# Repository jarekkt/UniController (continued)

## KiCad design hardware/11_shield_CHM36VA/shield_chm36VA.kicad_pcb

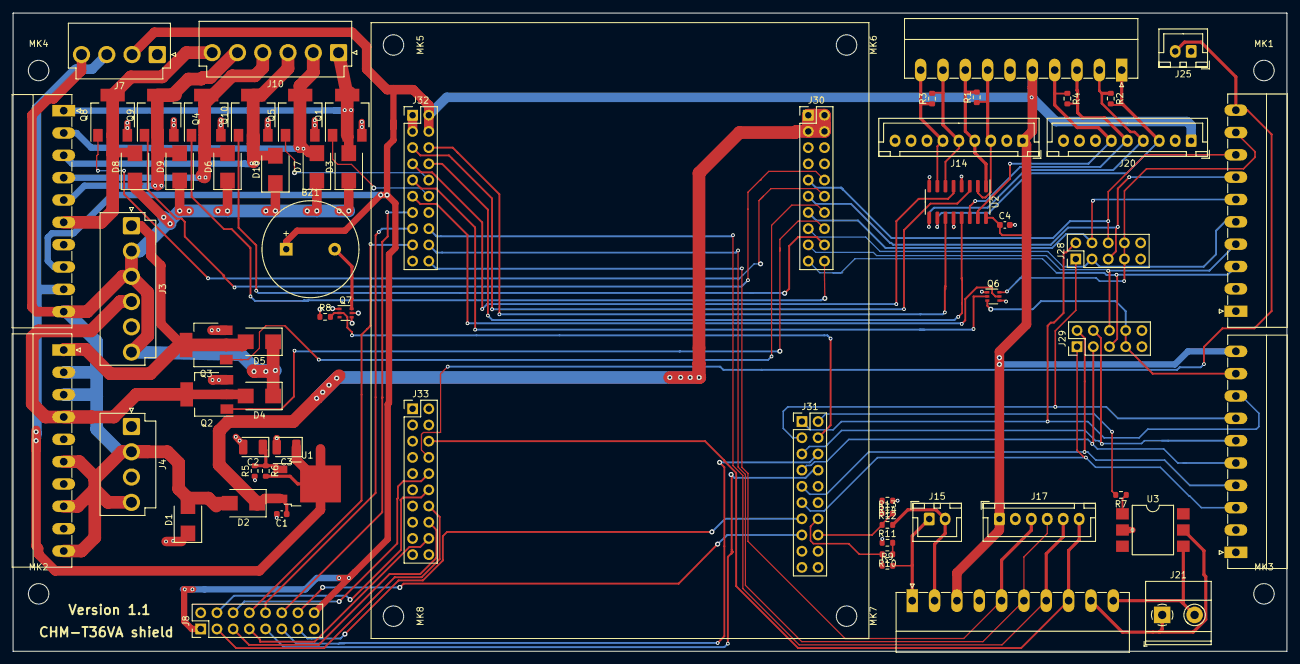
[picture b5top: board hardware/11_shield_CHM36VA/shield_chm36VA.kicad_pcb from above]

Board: 2 copper layers, 199.6 x 100.0 mm, 73 parts (0 on the bottom side), 80 nets.

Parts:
BZ1: Buzzer; Buzzer_15x7.5RM7.6
C1, C4: 100n; C_0603_1608Metric
C2: 10uf; CP_EIA-3528-21_Kemet-B
C3: 1uf; CP_EIA-3528-21_Kemet-B
D1: SMCJ24CA; D_SMB
D2, D3, D4, D5, D6, D7, D8, D9, D10: SK56; D_SMB
J3, J10: Conn_01x06_Male; JST_VH_B6P-VH-B_1x06_P3.96mm_Vertical
J4, J7: Conn_01x04_Male; JST_VH_B4P-VH_1x04_P3.96mm_Vertical
J5, J11, J12, J23, J26, J27: Conn_01x10_Male; PhoenixContact_MC-G_10x3.50mm_Angled
J8: Conn_02x05_Odd_Even; PinHeader_2x08_P2.54mm_Vertical
J14, J20: Conn_01x09_Male; JST_XH_B9B-XH-A_1x09_P2.50mm_Vertical
J15, J25: Conn_01x02_Male; JST_XH_B2B-XH-A_1x02_P2.50mm_Vertical
J17: Conn_01x06_Male; JST_XH_B6B-XH-A_1x06_P2.50mm_Vertical
J21: Conn_01x02_Male; TerminalBlock_Phoenix_MKDS-1,5-2-5.08_1x02_P5.08mm_Horizont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
J28, J29: Conn_02x05_Odd_Even; PinHeader_2x05_P2.54mm_Vertical
J30, J31, J33: Conn_02x20_Odd_Even; PinHeader_2x10_P2.54mm_Vertical
J32: Conn_02x10_Odd_Even; PinHeader_2x10_P2.54mm_Vertical
MK1, MK1#2, MK2, MK2#2, MK3, MK3#2, MK6, MK6#2: Mounting_Hole; MountingHole_3.2mm_M3
Q1, Q2, Q3, Q4, Q5, Q8, Q9, Q10: IRLL2705PBF; SOT-223
Q6, Q7: BSS138BKS; SOT-363_SC-70-6
R1, R2, R3, R4: 120R; R_0603_1608Metric
R5, R8: 4k6; R_0603_1608Metric
R6: 1k; R_0603_1608Metric
R7: 220R; R_0603_1608Metric
R9, R10, R11, R12, R13, R14: 2k2; R_0603_1608Metric
U1: LM217_TO-252; TO-252-2
U2: AM26LS32ACD; SOIC-16_3.9x9.9mm_P1.27mm
U3: CNY17-1; SMDIP-6_W9.53mm

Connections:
+3V3: J32.1, J32.3
+5V: BZ1.1 (-), C4.1, J7.2, J8.1, J8.16, J11.8, J12.3, J14.1, J17.1, J20.1, J23.5, J27.10, J32.2, J32.4, U2.16 (VDD)
+7V: C3.1, J7.3, J11.9, R6.2, U1.2 (VO)
+24V: D1.2, D2.2 (A), D3.1 (K), D4.1 (K), D5.1 (K), D6.1 (K), D7.1 (K), D8.1 (K), D9.1 (K), D10.1 (K), J3.2, J3.3, J3.6, J4.2, J4.4, J5.2, J5.3, J5.6, J5.8, J5.10, J7.4, J11.10
/controller/CAM+: J12.9, J21.1, U3.5
/controller/CAM-: J12.10, J21.2, U3.4
/controller/DIR_A: J27.7, J28.1, J31.3
/controller/DIR_B: J27.5, J29.3, J31.7
/controller/DIR_C: J27.3, J29.1, J31.11
/controller/DIR_X: J26.7, J28.5, J30.11
/controller/DIR_Y: J26.5, J28.3, J30.15
/controller/DIR_Z: J26.3, J29.5, J30.19
/controller/ENA_ABC: J27.9, J29.7, J29.8, Q6.3 (D)
/controller/ENA_XYZ: J26.9, J28.7, J28.8, Q6.6 (D)
/controller/ENC_X_A+: J20.3, J23.1, R2.2, U2.10 (3A)
/controller/ENC_X_A-: J20.4, J23.2, R2.1, U2.9 (3B)
/controller/ENC_X_B+: J20.5, J23.3, R4.2, U2.14 (4A)
/controller/ENC_X_B-: J20.6, J23.4, R4.1, U2.15 (4B)
/controller/ENC_Y_A+: J14.3, J23.7, R1.1, U2.2 (1A)
/controller/ENC_Y_A-: J14.4, J23.8, R1.2, U2.1 (1B)
/controller/ENC_Y_B+: J14.5, J23.9, R3.2, U2.6 (2A)
/controller/ENC_Y_B-: J14.6, J23.10, R3.1, U2.7 (2B)
/controller/ESTOP: J25.2, J26.10, J33.8
/controller/IN1_ANA: J12.1, J15.1, R9.2
/controller/IN2_ANA: J12.2, J15.2, R12.2
/controller/IN_LZ_LIM: J12.8, J17.6, J33.6
/controller/IN_X_LIM: J12.7, J17.5, J32.16
/controller/IN_Y_LIM: J12.6, J17.4, J32.18
/controller/IN_Z_LIM: J12.5, J17.3, J32.20
/controller/OUT_LED_DN: D9.2 (A), J10.5, J11.5, Q9.2 (D), Q9.4 (D)
/controller/OUT_LED_UP: D8.2 (A), J10.6, J11.6, Q8.2 (D), Q8.4 (D)
/controller/OUT_LZ: D3.2 (A), J10.1, J11.1, Q1.2 (D), Q1.4 (D)
/controller/OUT_N1_VALVE: D6.2 (A), J10.4, J11.4, Q4.2 (D), Q4.4 (D)
/controller/OUT_N2_VALVE: D10.2 (A), J10.3, J11.3, Q10.2 (D), Q10.4 (D)
/controller/OUT_UNUSED: D7.2 (A), J10.2, J11.2, Q5.2 (D), Q5.4 (D)
/controller/PUMP_PRESS: D5.2 (A), J3.1, J5.1, Q3.2 (D), Q3.4 (D)
/controller/PUMP_VACUUM: D4.2 (A), J3.4, J5.4, Q2.2 (D), Q2.4 (D)
/controller/SPARE_DIR_D: J8.14, J31.15
/controller/SPARE_IN6: J8.6, J33.10
/controller/SPARE_IN7: J8.4, J33.12
/controller/SPARE_IN8: J8.3, J33.14
/controller/SPARE_IN9: J8.5, J33.16
/controller/SPARE_IN10: J8.7, J33.18
/controller/SPARE_IO3: J8.12, J32.13
/controller/SPARE_IO4: J8.10, J32.15
/controller/SPARE_IO5: J8.8, J32.17
/controller/SPARE_OUT10: J8.11, J31.6
/controller/SPARE_OUT11: J8.9, J31.8
/controller/SPARE_STEP_D: J8.13, J31.13
/controller/STEP_A: J27.8, J28.2, J31.1
/controller/STEP_B: J27.6, J29.4, J31.5
/controller/STEP_C: J27.4, J29.2, J31.9
/controller/STEP_X: J26.8, J28.6, J30.9
/controller/STEP_Y: J26.6, J28.4, J30.13
/controller/STEP_Z: J26.4, J29.6, J30.17
/controller/UniPrinterBase/ADC.CH1: J31.14, R9.1, R10.2
/controller/UniPrinterBase/ADC.CH2: J31.16, R12.1, R13.2
/controller/UniPrinterBase/ENC1.CH1: J32.5, U2.3 (1Y)
/controller/UniPrinterBase/ENC1.CH2: J32.7, U2.5 (2Y)
/controller/UniPrinterBase/ENC2.CH1: J32.6, U2.11 (3Y)
/controller/UniPrinterBase/ENC2.CH2: J32.8, U2.13 (4Y)
/controller/UniPrinterBase/ENC3_CH1.OUT_CPU11_PWM: J32.10, Q5.1 (G)
/controller/UniPrinterBase/ENC3_CH2.OUT_CPU12_PWM: J32.12, Q1.1 (G)
/controller/UniPrinterBase/IO_CPU1: J32.9, Q6.2 (G)
/controller/UniPrinterBase/IO_CPU2: J32.11, Q6.5 (G)
/controller/UniPrinterBase/OUT_CPU1_PWM: J30.10, Q9.1 (G)
/controller/UniPrinterBase/OUT_CPU2_PWM: J30.12, Q8.1 (G)
/controller/UniPrinterBase/OUT_CPU3_PWM: J30.14, Q3.1 (G)
/controller/UniPrinterBase/OUT_CPU4_PWM: J30.16, Q2.1 (G)
/controller/UniPrinterBase/OUT_CPU5: J30.18, Q10.1 (G)
/controller/UniPrinterBase/OUT_CPU6: J30.20, Q4.1 (G)
/controller/UniPrinterBase/OUT_CPU7: J31.2, R7.2
/controller/UniPrinterBase/OUT_CPU8: J31.4, Q7.2 (G), R8.2
/controller/VSUP: C1.1, D2.1 (K), J30.1, J30.2, J30.3, J30.4, U1.3 (VI)
GND: C1.2, C2.2, C3.2, C4.2, D1.1, J3.5, J4.1, J4.3, J5.5, J5.7, J5.9, J7.1, J8.2, J8.15, J11.7, J12.4, J14.2, J17.2, J20.2, J23.6, J25.1, J26.1, J26.2, J27.1, J27.2, J28.9, J28.10, J29.9, J29.10, J30.5, J30.6, J30.7, J30.8, J33.1, J33.2, J33.3, J33.4, Q1.3 (S), Q2.3 (S), Q3.3 (S), Q4.3 (S), Q5.3 (S), Q6.1 (S), Q6.4 (S), Q7.1 (S), Q7.4 (S), Q7.5 (G), Q8.3 (S), Q9.3 (S), Q10.3 (S), R5.1, R8.1, R11.1, R14.1, U2.4 (G), U2.8 (GND), U2.12 (~G), U3.2
unnamed: BZ1.2 (+), Q7.6 (D)
unnamed: C2.1, R5.2, R6.1, U1.1 (ADJ)
unnamed: R7.1, U3.1
unnamed: R10.1, R11.2
unnamed: R13.1, R14.2

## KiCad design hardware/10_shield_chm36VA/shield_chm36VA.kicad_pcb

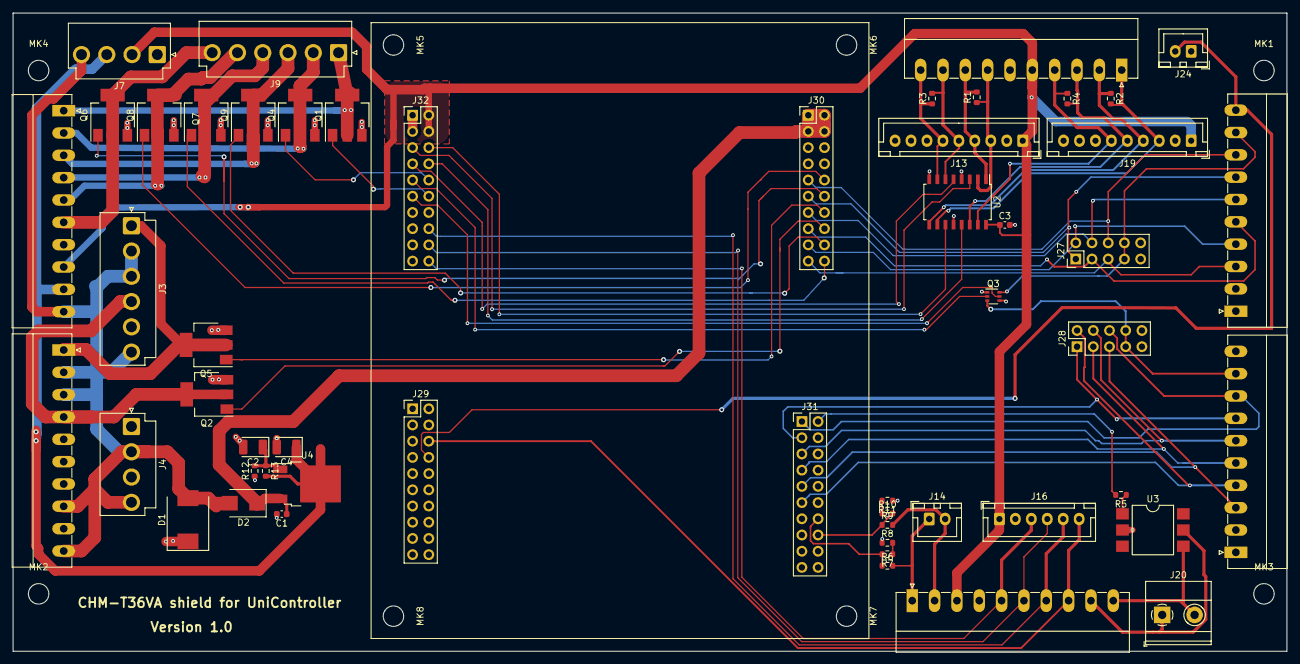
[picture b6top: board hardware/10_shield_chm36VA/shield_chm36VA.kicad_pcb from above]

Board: 2 copper layers, 199.6 x 100.0 mm, 61 parts (0 on the bottom side), 66 nets.

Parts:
C1, C3: 100n; C_0603_1608Metric
C2: 10uf; CP_EIA-3528-21_Kemet-B
C4: 1uf; CP_EIA-3528-21_Kemet-B
D1: SMCJ24CA; D_SMC
D2: SK56; D_SMB
J3, J9: Conn_01x06_Male; JST_VH_B6P-VH-B_1x06_P3.96mm_Vertical
J4, J7: Conn_01x04_Male; JST_VH_B4P-VH_1x04_P3.96mm_Vertical
J5, J10, J11, J22, J25, J26: Conn_01x10_Male; PhoenixContact_MC-G_10x3.50mm_Angled
J13, J19: Conn_01x09_Male; JST_XH_B9B-XH-A_1x09_P2.50mm_Vertical
J14, J24: Conn_01x02_Male; JST_XH_B2B-XH-A_1x02_P2.50mm_Vertical
J16: Conn_01x06_Male; JST_XH_B6B-XH-A_1x06_P2.50mm_Vertical
J20: Conn_01x02_Male; TerminalBlock_Phoenix_MKDS-1,5-2-5.08_1x02_P5.08mm_Horizont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
J27, J28: Conn_02x05_Odd_Even; PinHeader_2x05_P2.54mm_Vertical
J29, J30, J31: Conn_02x20_Odd_Even; PinHeader_2x10_P2.54mm_Vertical
J32: Conn_02x10_Odd_Even; PinHeader_2x10_P2.54mm_Vertical
MK1, MK1#2, MK2, MK2#2, MK3, MK3#2, MK6, MK6#2: Mounting_Hole; MountingHole_3.2mm_M3
Q1, Q2, Q4, Q5, Q6, Q7, Q8, Q9: IRLL2705PBF; SOT-223
Q3: BSS138BKS; SOT-363_SC-70-6
R1, R2, R3, R4: 120R; R_0603_1608Metric
R5: 220R; R_0603_1608Metric
R6, R7, R8, R9, R10, R11: 2k2; R_0603_1608Metric
R12: 4k6; R_0603_1608Metric
R13: 1k; R_0603_1608Metric
U2: AM26LV32xNS; SOIC-16W_5.3x10.2mm_P1.27mm
U3: CNY17-1; SMDIP-6_W9.53mm
U4: LM217_TO-252; TO-252-2

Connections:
+3V3: J32.1, J32.3
+5V: C3.1, J7.2, J10.8, J11.3, J13.1, J16.1, J19.1, J22.5, J32.2, J32.4, U2.16 (VDD)
+7V: C4.1, J7.3, J10.9, R13.2, U4.2 (VO)
+24V: D1.2, D2.2 (A), J3.2, J3.3, J3.6, J4.2, J4.4, J5.2, J5.3, J5.8, J5.10, J7.4, J10.10
/controller/CAM+: J11.9, J20.1, U3.5
/controller/CAM-: J11.10, J20.2, U3.4
/controller/DIR_B: J26.7, J28.1, J31.3
/controller/DIR_C: J26.5, J28.3, J31.7
/controller/DIR_D: J26.3, J28.5, J31.9
/controller/DIR_X: J25.7, J27.1, J30.11
/controller/DIR_Y: J25.5, J27.3, J30.15
/controller/DIR_Z: J25.3, J27.5, J30.19
/controller/ENA_BCD: J26.9, J28.7, J28.8, Q3.3 (D)
/controller/ENA_XYZ: J25.9, J27.7, J27.8, Q3.6 (D)
/controller/ENC_X_A+: J19.3, J22.1, R2.2, U2.10 (3A)
/controller/ENC_X_A-: J19.4, J22.2, R2.1, U2.9 (3B)
/controller/ENC_X_B+: J19.5, J22.3, R4.2, U2.14 (4A)
/controller/ENC_X_B-: J19.6, J22.4, R4.1, U2.15 (4B)
/controller/ENC_Y_A+: J13.3, J22.7, R1.1, U2.2 (1A)
/controller/ENC_Y_A-: J13.4, J22.8, R1.2, U2.1 (1B)
/controller/ENC_Y_B+: J13.5, J22.9, R3.2, U2.6 (2A)
/controller/ENC_Y_B-: J13.6, J22.10, R3.1, U2.7 (2B)
/controller/ESTOP: J24.2, J25.10, J29.8
/controller/IN1_ANA: J11.1, J14.1, R6.2
/controller/IN2_ANA: J11.2, J14.2, R9.2
/controller/IN_LZ_LIM: J11.8, J16.6, J29.6
/controller/IN_X_LIM: J11.7, J16.5, J32.16
/controller/IN_Y_LIM: J11.6, J16.4, J32.18
/controller/IN_Z_LIM: J11.5, J16.3, J32.20
/controller/OUT_LED_DN: J9.5, J10.5, Q8.2 (D), Q8.4 (D)
/controller/OUT_LED_UP: J9.6, J10.6, Q6.2 (D), Q6.4 (D)
/controller/OUT_LZ: J9.1, J10.1, Q1.2 (D), Q1.4 (D)
/controller/OUT_N1_VALVE: J9.4, J10.4, Q7.2 (D), Q7.4 (D)
/controller/OUT_N2_VALVE: J9.3, J10.3, Q9.2 (D), Q9.4 (D)
/controller/OUT_UNUSED: J9.2, J10.2, Q4.2 (D), Q4.4 (D)
/controller/PUMP_PRESS: J3.1, J5.1, Q5.2 (D), Q5.4 (D)
/controller/PUMP_VACUUM: J3.4, J5.4, Q2.2 (D), Q2.4 (D)
/controller/STEP_B: J26.8, J28.6, J31.1
/controller/STEP_C: J26.6, J28.4, J31.5
/controller/STEP_D: J26.4, J28.2, J31.11
/controller/STEP_X: J25.8, J27.6, J30.9
/controller/STEP_Y: J25.6, J27.4, J30.13
/controller/STEP_Z: J25.4, J27.2, J30.17
/controller/UniPrinterBase/ADC.CH1: J31.14, R6.1, R7.2
/controller/UniPrinterBase/ADC.CH2: J31.16, R9.1, R10.2
/controller/UniPrinterBase/ENC1.CH1: J32.5, U2.3 (1Y)
/controller/UniPrinterBase/ENC1.CH2: J32.7, U2.5 (2Y)
/controller/UniPrinterBase/ENC2.CH1: J32.6, U2.11 (3Y)
/controller/UniPrinterBase/ENC2.CH2: J32.8, U2.13 (4Y)
/controller/UniPrinterBase/ENC3_CH1.OUT_CPU11_PWM: J32.10, Q4.1 (G)
/controller/UniPrinterBase/ENC3_CH2.OUT_CPU12_PWM: J32.12, Q1.1 (G)
/controller/UniPrinterBase/IO_CPU1: J32.9, Q3.2 (G)
/controller/UniPrinterBase/IO_CPU2: J32.11, Q3.5 (G)
/controller/UniPrinterBase/OUT_CPU1_PWM: J30.10, Q8.1 (G)
/controller/UniPrinterBase/OUT_CPU2_PWM: J30.12, Q6.1 (G)
/controller/UniPrinterBase/OUT_CPU3_PWM: J30.14, Q5.1 (G)
/controller/UniPrinterBase/OUT_CPU4_PWM: J30.16, Q2.1 (G)
/controller/UniPrinterBase/OUT_CPU5: J30.18, Q9.1 (G)
/controller/UniPrinterBase/OUT_CPU6: J30.20, Q7.1 (G)
/controller/UniPrinterBase/OUT_CPU7: J31.2, R5.2
/controller/VSUP: C1.1, D2.1 (K), J30.1, J30.2, J30.3, J30.4, U4.3 (VI)
GND: C1.2, C2.2, C3.2, C4.2, D1.1, J3.5, J4.1, J4.3, J5.5, J5.7, J5.9, J7.1, J10.7, J11.4, J13.2, J16.2, J19.2, J22.6, J24.1, J25.1, J25.2, J26.1, J26.2, J27.9, J27.10, J28.9, J28.10, J29.1, J29.2, J29.3, J29.4, J30.5, J30.6, J30.7, J30.8, Q1.3 (S), Q2.3 (S), Q3.1 (S), Q3.4 (S), Q4.3 (S), Q5.3 (S), Q6.3 (S), Q7.3 (S), Q8.3 (S), Q9.3 (S), R8.1, R11.1, R12.1, U2.4 (G), U2.8 (GND), U2.12 (~G), U3.2
unnamed: C2.1, R12.2, R13.1, U4.1 (ADJ)
unnamed: R5.1, U3.1
unnamed: R7.1, R8.2
unnamed: R10.1, R11.2

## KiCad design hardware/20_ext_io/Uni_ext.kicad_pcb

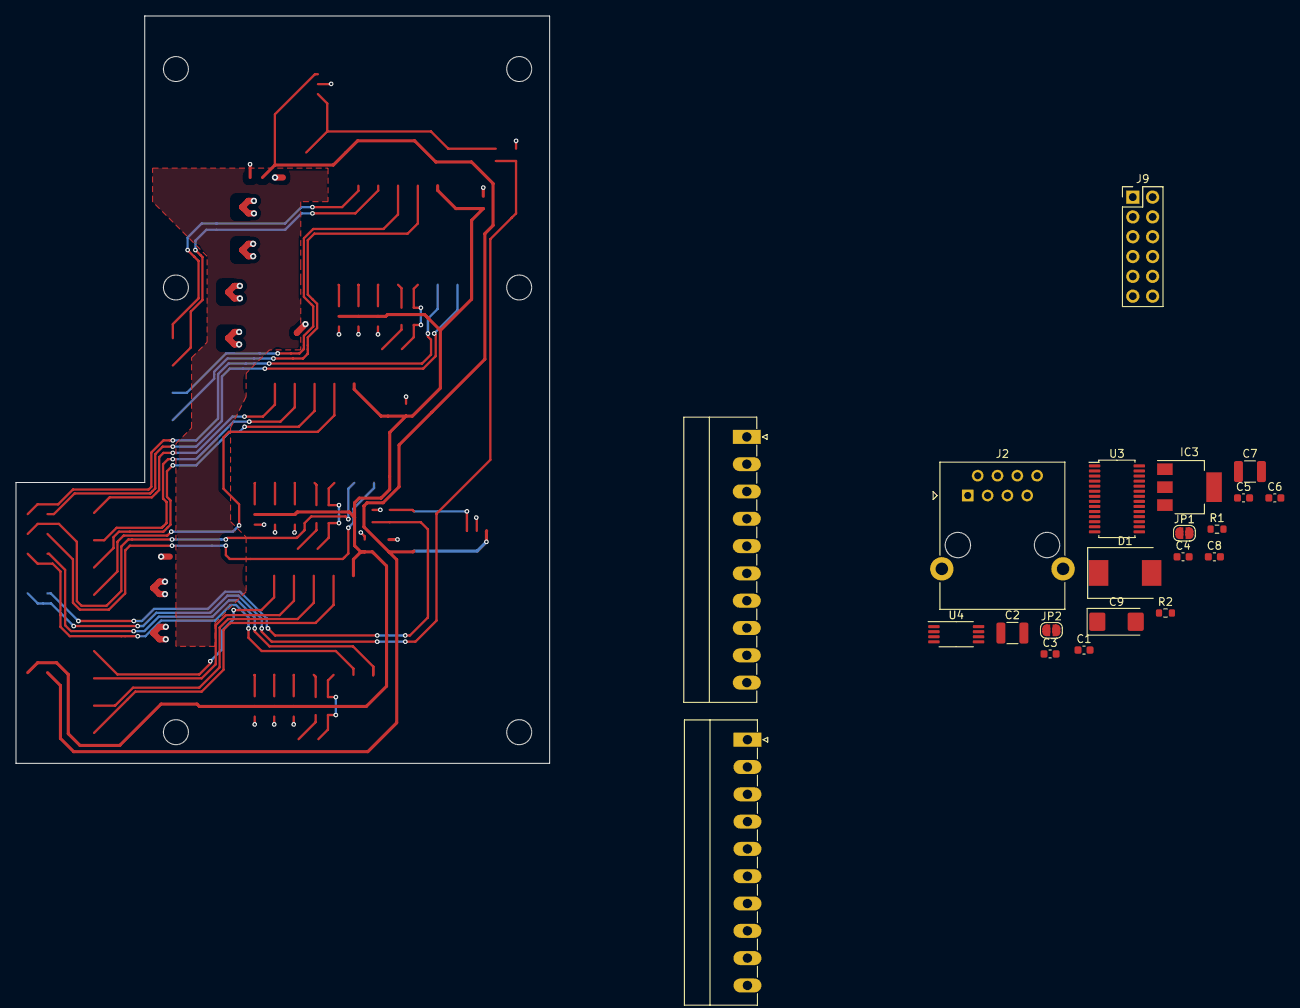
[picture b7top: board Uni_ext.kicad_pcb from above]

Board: 2 copper layers, 68.4 x 95.8 mm, 27 parts (0 on the bottom side), 13 nets.

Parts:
C1, C3, C5, C8: 100n; C_0603_1608Metric
C2: 10uF 50V; C_1210_3225Metric
C4: 5.6nF; C_0603_1608Metric
C6: 2.2uF; C_0603_1608Metric
C7: 22uF 25V; C_1210_3225Metric
C9: 100uF 6.3V Tantal; CP_EIA-6032-28_Kemet-C
D1: SMCJ24CA; D_SMC
IC3: TLV1117-33; SOT-223-3_TabPin2
J1, J7: Conn_01x10; PhoenixContact_MC-G_10x3.50mm_Angled
J2: RJ45_Shielded; RJ45_Ninigi_GE
J9: Conn_02x16_Odd_Even; PinHeader_2x06_P2.54mm_Vertical
JP1, JP2: IN2_P; SolderJumper-2_P1.3mm_Open_RoundedPad1.0x1.5mm
MK1, MK2, MK3, MK4, MK5, MK6: Mounting_Hole; MountingHole_3.2mm_M3
R1: 178k; R_0603_1608Metric
R2: 39k; R_0603_1608Metric
U3: PCA9685PW; TSSOP-28_4.4x9.7mm_P0.65mm
U4: P82B96; TSSOP-8_4.4x3mm_P0.65mm

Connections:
+3V3: C9.1, IC3.2 (OUT), J9.9
+5V: C1.1, C5.1, C7.1, C8.2, IC3.3 (IN), J9.7, JP1.1 (A), JP2.2 (B), R1.1, U3.28 (VDD), U4.8 (VCC)
/I2C.SCL: U3.26 (SCL), U4.7 (SCL)
/I2C.SDA: U3.27 (SDA), U4.1 (SDA)
/SCL_RX: J2.7, U4.6 (RXD-SCL)
/SCL_TX: J2.8, U4.5 (TXD-SCL)
/SDA_RX: J2.3, U4.2 (RXD-SDA)
/SDA_TX: J2.6, U4.3 (TXD-SDA)
/SUPPLY_24V: C2.1, D1.2 (A2), J1.2
GND: C1.2, C2.2, C4.1, C5.2, C6.2, C7.2, C8.1, C9.2, D1.1 (A1), IC3.1 (GND), J1.1, J2.SH, J9.8, J9.10, R2.2, U3.3 (A2), U3.4 (A3), U3.5 (A4), U3.14 (VSS), U3.23 (~OE), U3.24 (A5), U3.25 (EXTCLK), U4.4 (GND)
unnamed: R1.2, R2.1
unnamed: JP1.2 (B), U3.1 (A0)
unnamed: JP2.1 (A), U3.2 (A1)

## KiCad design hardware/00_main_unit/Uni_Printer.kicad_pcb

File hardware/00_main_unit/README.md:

# UniController
# UniController

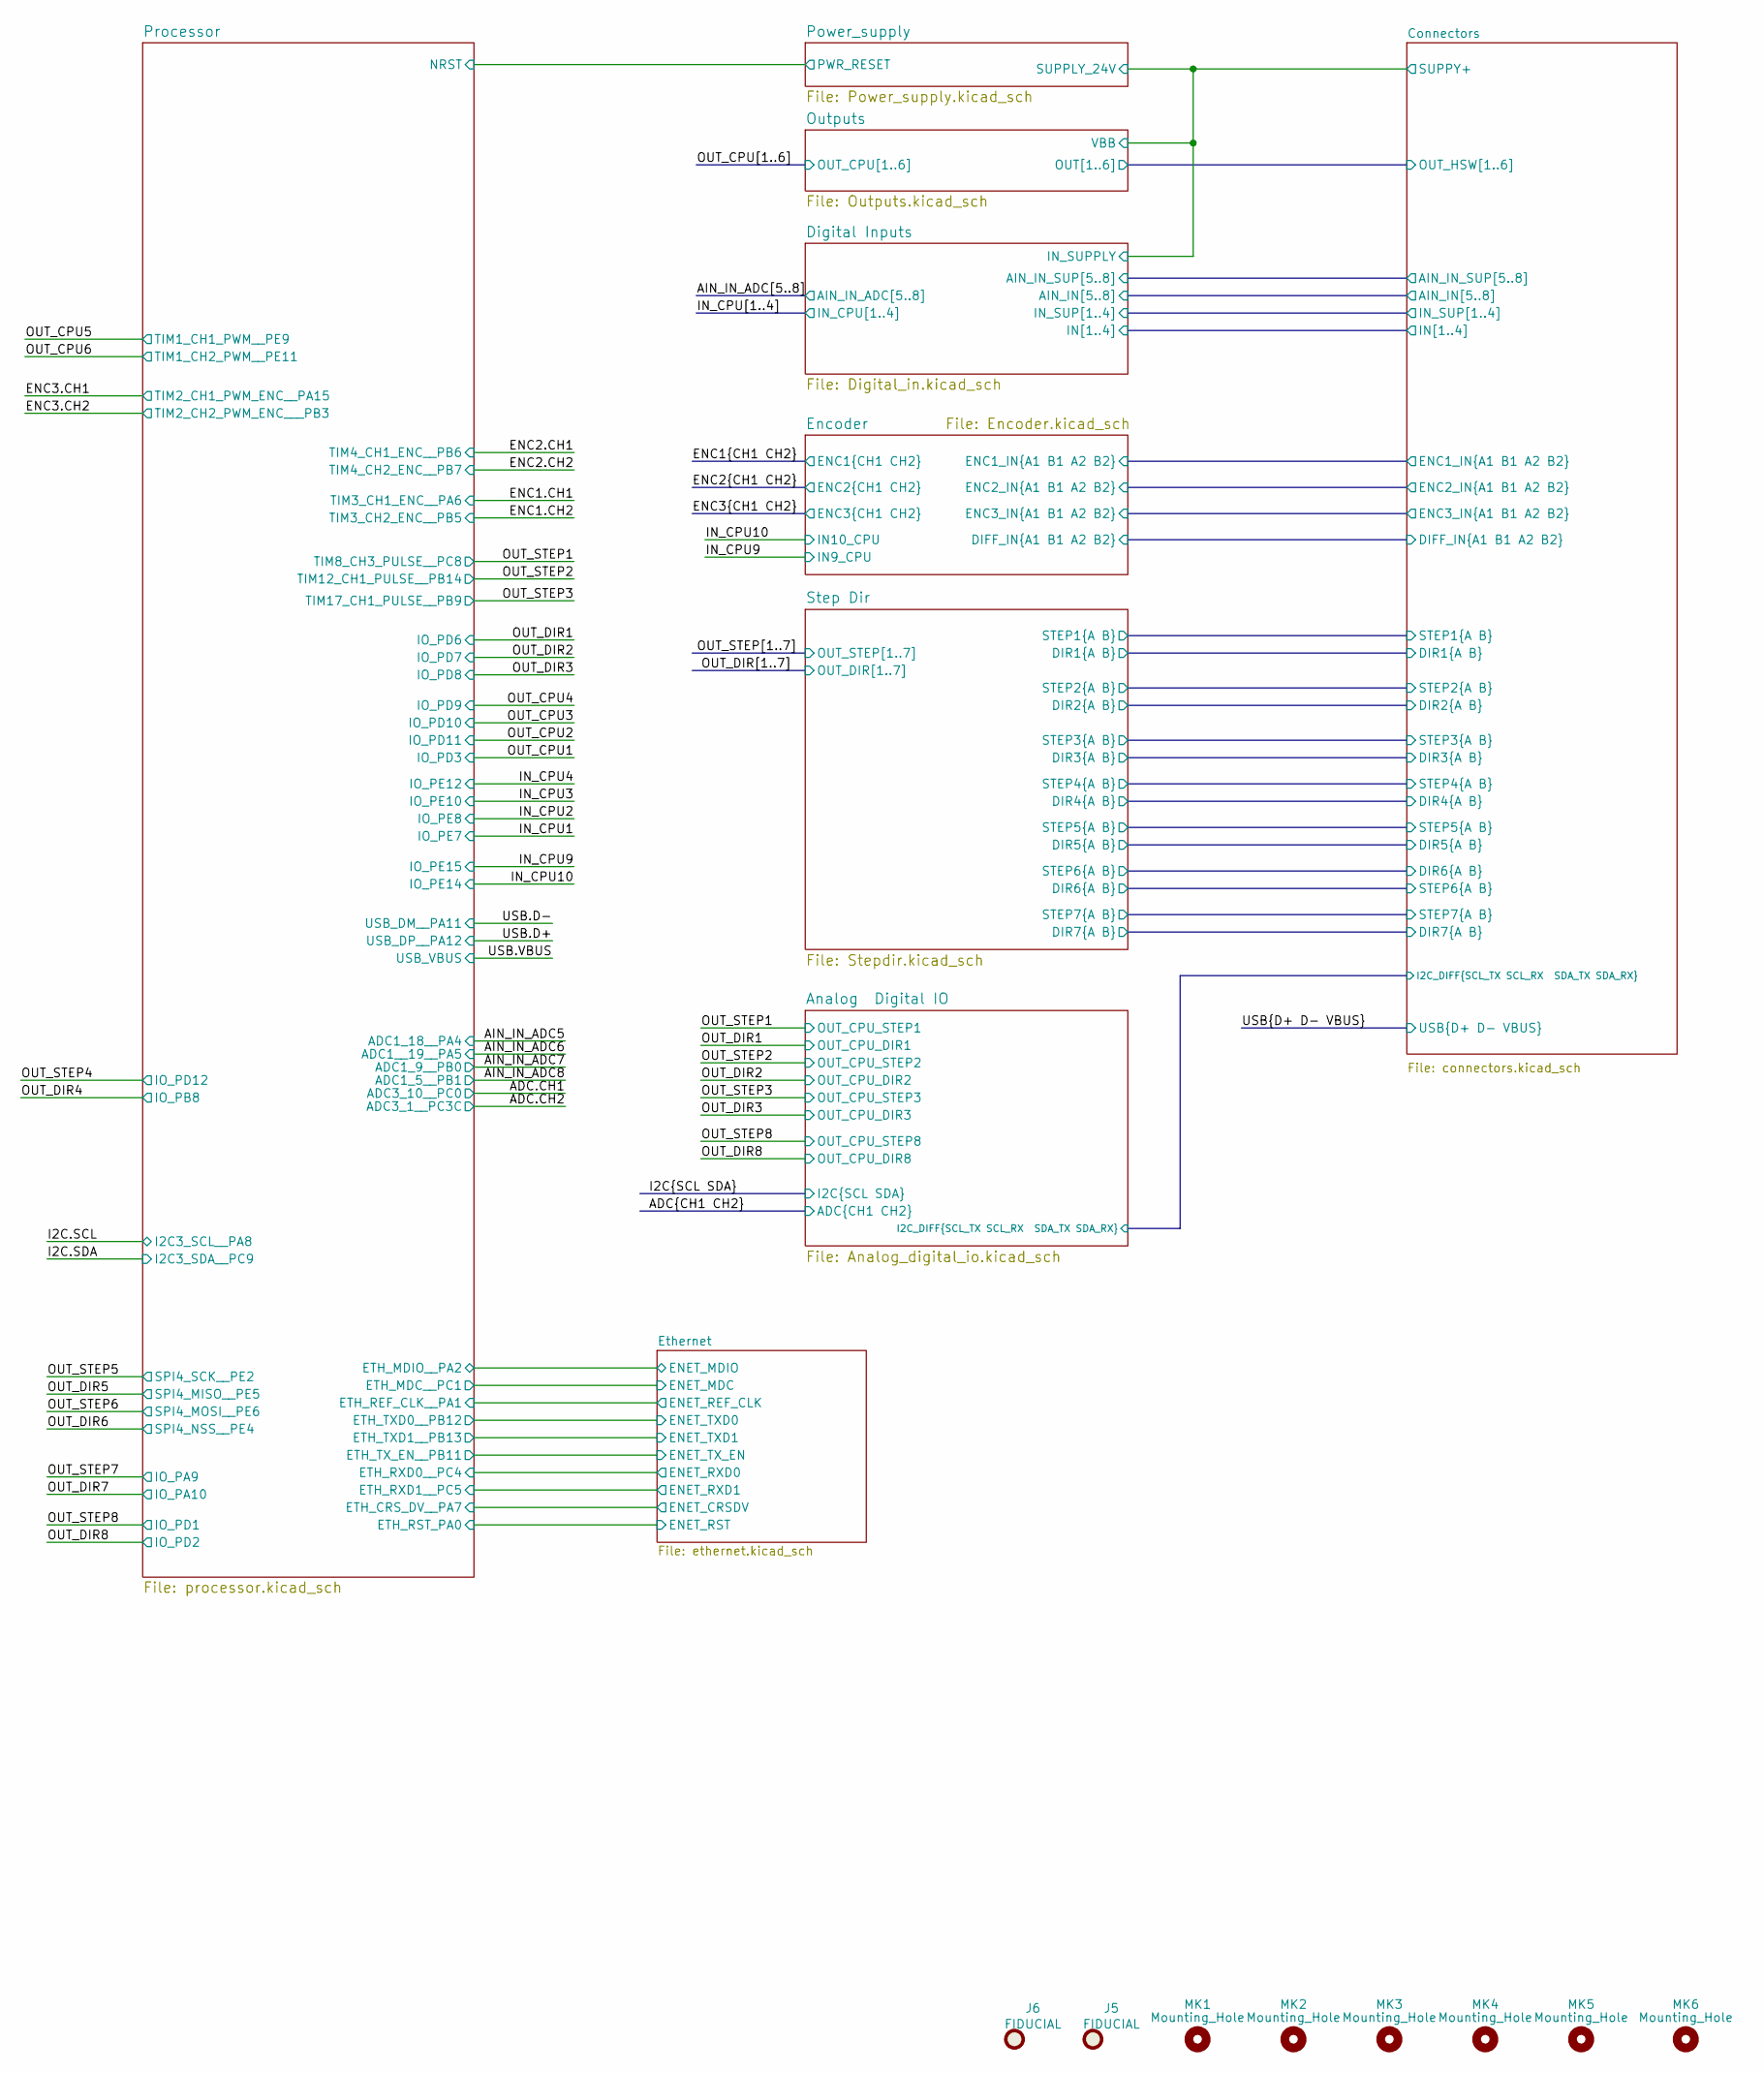
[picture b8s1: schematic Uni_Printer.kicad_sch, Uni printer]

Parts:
J5, J6: FIDUCIAL; Fiducial_1mm_Dia_2mm_Outer
MK1, MK2, MK3, MK4, MK5, MK6: Mounting_Hole; MountingHole_3.2mm_M3

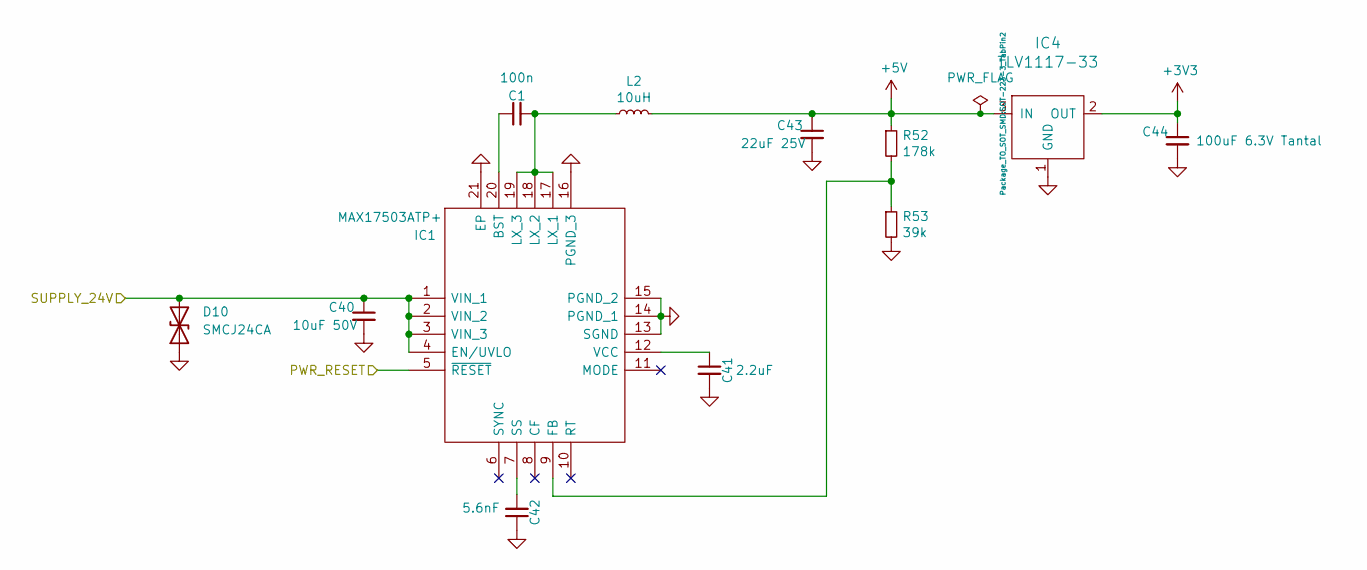
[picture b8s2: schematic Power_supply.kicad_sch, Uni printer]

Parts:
C1: 100n; C_0603_1608Metric
C40: 10uF 50V; C_1210_3225Metric
C41: 2.2uF; C_0603_1608Metric
C42: 5.6nF; C_0603_1608Metric
C43: 22uF 25V; C_1210_3225Metric
C44: 100uF 6.3V Tantal; CP_EIA-6032-28_Kemet-C
D10: SMCJ24CA; D_SMC
IC1: MAX17503ATP+; QFN50P400X400X80-21N; Manufacturer_Part_Number MAX17503ATP+; Mouser Part Number 700-MAX17503ATP+
IC4: TLV1117-33; SOT-223-3_TabPin2
L2: 10uH; HPI0630
R52: 178k; R_0603_1608Metric
R53: 39k; R_0603_1608Metric

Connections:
+5V: C43.1, IC4.3 (IN), L2.2, R52.1; also elsewhere on the board
/Connectors/SUPPY+: C40.1, D10.2 (A2), IC1.1 (VIN_1), IC1.2 (VIN_2), IC1.3 (VIN_3), IC1.4 (EN/UVLO); also elsewhere on the board
/Processor/NRST: IC1.5 (~RESET); also elsewhere on the board
unnamed: C1.1, IC1.20 (BST)
unnamed: C1.2, IC1.17 (LX_1), IC1.18 (LX_2), IC1.19 (LX_3), L2.1
unnamed: C41.1, IC1.12 (VCC)
unnamed: C42.2, IC1.7 (SS)
unnamed: IC1.9 (FB), R52.2, R53.1

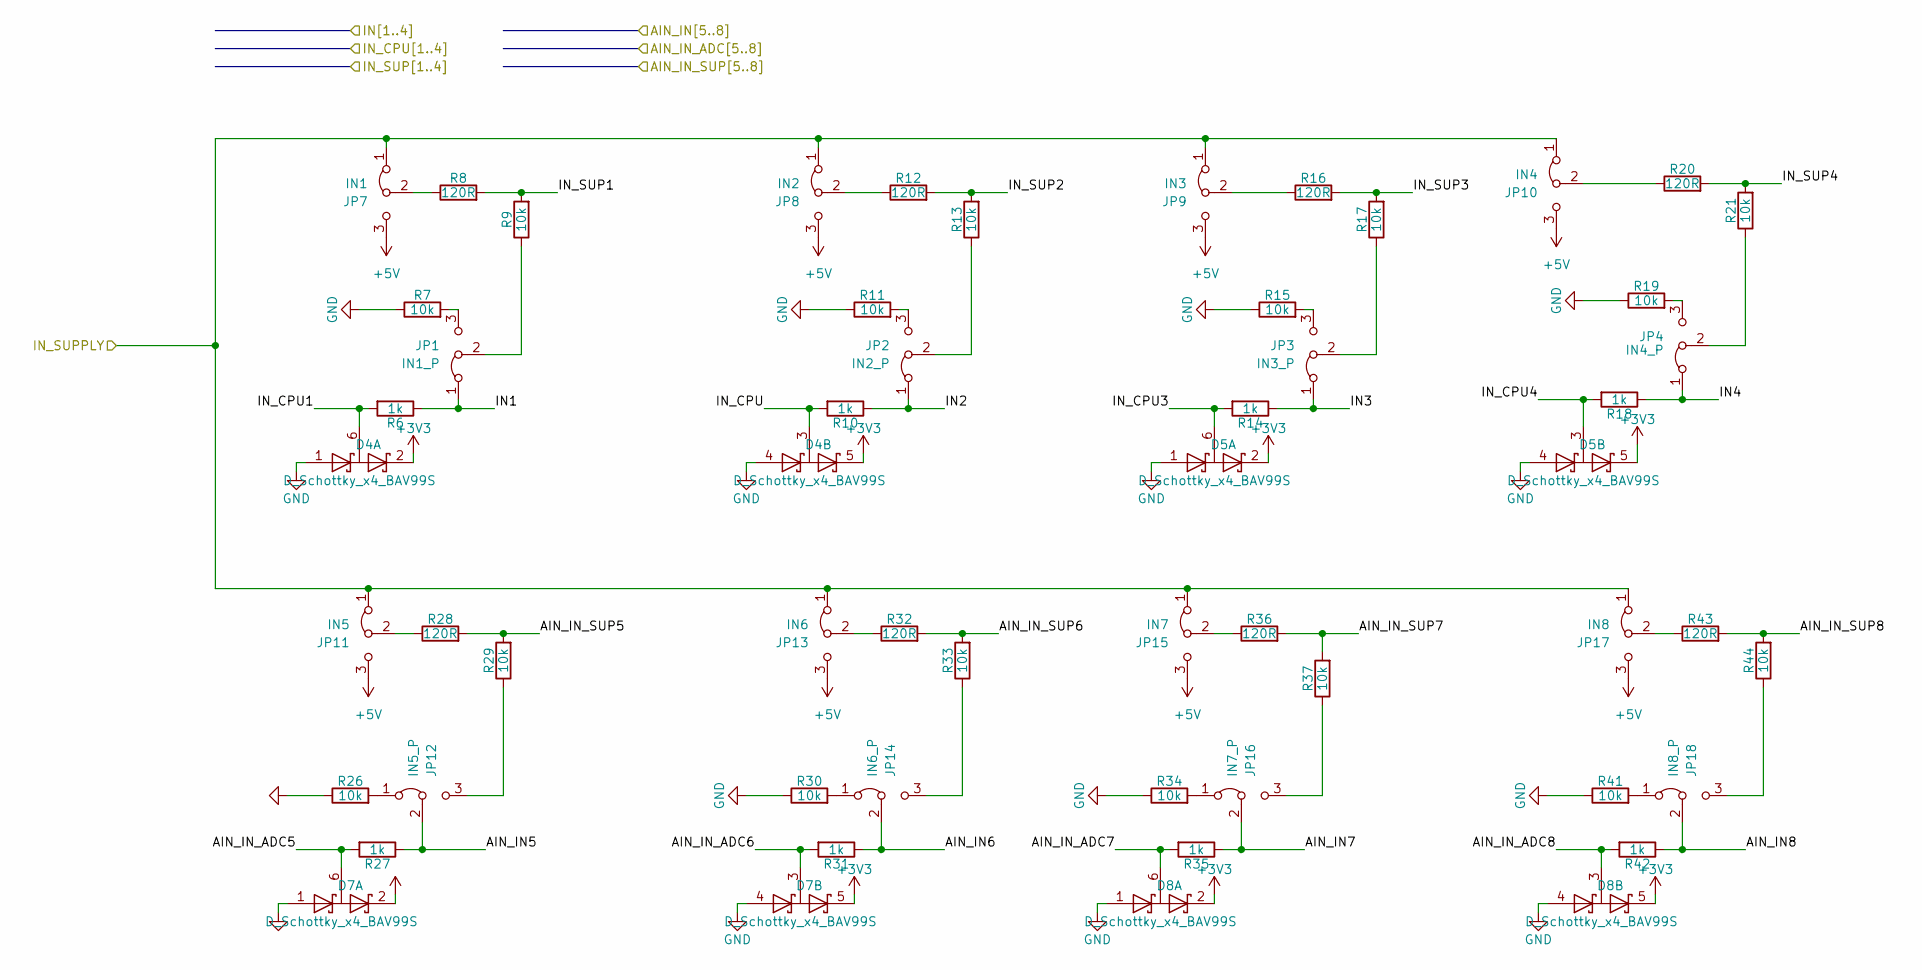
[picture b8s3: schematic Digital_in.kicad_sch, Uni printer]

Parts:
D4, D5, D7, D8: D_Schottky_x4_BAV99S; SOT-363
JP1: IN1_P; SolderJumper-3-open
JP2: IN2_P; SolderJumper-3-open
JP3: IN3_P; SolderJumper-3-open
JP4: IN4_P; SolderJumper-3-open
JP7: IN1; SolderJumper-3-open
JP8: IN2; SolderJumper-3-open
JP9: IN3; SolderJumper-3-open
JP10: IN4; SolderJumper-3-open
JP11: IN5; SolderJumper-3-open
JP12: IN5_P; SolderJumper-3-open
JP13: IN6; SolderJumper-3-open
JP14: IN6_P; SolderJumper-3-open
JP15: IN7; SolderJumper-3-open
JP16: IN7_P; SolderJumper-3-open
JP17: IN8; SolderJumper-3-open
JP18: IN8_P; SolderJumper-3-open
R6, R10, R14, R18, R27, R31, R35, R42: 1k; R_0603_1608Metric
R7, R9, R11, R13, R15, R17, R19, R21, R26, R29, R30, R33, R34, R37, R41, R44: 10k; R_0603_1608Metric
R8, R12, R16, R20, R28, R32, R36, R43: 120R; R_0603_1608Metric

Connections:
+5V: JP7.3 (B), JP8.3 (B), JP9.3 (B), JP10.3 (B), JP11.3 (B), JP13.3 (B), JP15.3 (B), JP17.3 (B); also elsewhere on the board
/AIN_IN_ADC5: D7.6 (C), R27.2; also elsewhere on the board
/AIN_IN_ADC6: D7.3 (C), R31.2; also elsewhere on the board
/AIN_IN_ADC7: D8.6 (C), R35.2; also elsewhere on the board
/AIN_IN_ADC8: D8.3 (C), R42.2; also elsewhere on the board
/Connectors/AIN_IN5: JP12.2 (C), R27.1; also elsewhere on the board
/Connectors/AIN_IN6: JP14.2 (C), R31.1; also elsewhere on the board
/Connectors/AIN_IN7: JP16.2 (C), R35.1; also elsewhere on the board
/Connectors/AIN_IN8: JP18.2 (C), R42.1; also elsewhere on the board
/Connectors/AIN_IN_SUP5: R28.2, R29.2; also elsewhere on the board
/Connectors/AIN_IN_SUP6: R32.2, R33.2; also elsewhere on the board
/Connectors/AIN_IN_SUP7: R36.2, R37.2; also elsewhere on the board
/Connectors/AIN_IN_SUP8: R43.2, R44.2; also elsewhere on the board
/Connectors/IN1: JP1.1 (A), R6.1; also elsewhere on the board
/Connectors/IN2: JP2.1 (A), R10.1; also elsewhere on the board
/Connectors/IN3: JP3.1 (A), R14.1; also elsewhere on the board
/Connectors/IN4: JP4.1 (A), R18.1; also elsewhere on the board
/Connectors/IN_SUP1: R8.2, R9.2; also elsewhere on the board
/Connectors/IN_SUP2: R12.2, R13.2; also elsewhere on the board
/Connectors/IN_SUP3: R16.2, R17.2; also elsewhere on the board
/Connectors/IN_SUP4: R20.2, R21.2; also elsewhere on the board
/Connectors/SUPPY+: JP7.1 (A), JP8.1 (A), JP9.1 (A), JP10.1 (A), JP11.1 (A), JP13.1 (A), JP15.1 (A), JP17.1 (A); also elsewhere on the board
/Digital Inputs/IN_CPU: D4.3 (C), R10.2
/IN_CPU1: D4.6 (C), R6.2; also elsewhere on the board
/IN_CPU3: D5.6 (C), R14.2; also elsewhere on the board
/IN_CPU4: D5.3 (C), R18.2; also elsewhere on the board
unnamed: JP1.2 (C), R9.1
unnamed: JP1.3 (B), R7.2
unnamed: JP2.2 (C), R13.1
unnamed: JP2.3 (B), R11.2
unnamed: JP3.2 (C), R17.1
unnamed: JP3.3 (B), R15.2
unnamed: JP4.2 (C), R21.1
unnamed: JP4.3 (B), R19.2
unnamed: JP7.2 (C), R8.1
unnamed: JP8.2 (C), R12.1
unnamed: JP9.2 (C), R16.1
unnamed: JP10.2 (C), R20.1
unnamed: JP11.2 (C), R28.1
unnamed: JP12.1 (A), R26.2
unnamed: JP12.3 (B), R29.1
unnamed: JP13.2 (C), R32.1
unnamed: JP14.1 (A), R30.2
unnamed: JP14.3 (B), R33.1
unnamed: JP15.2 (C), R36.1
unnamed: JP16.1 (A), R34.2
unnamed: JP16.3 (B), R37.1
unnamed: JP17.2 (C), R43.1
unnamed: JP18.1 (A), R41.2
unnamed: JP18.3 (B), R44.1

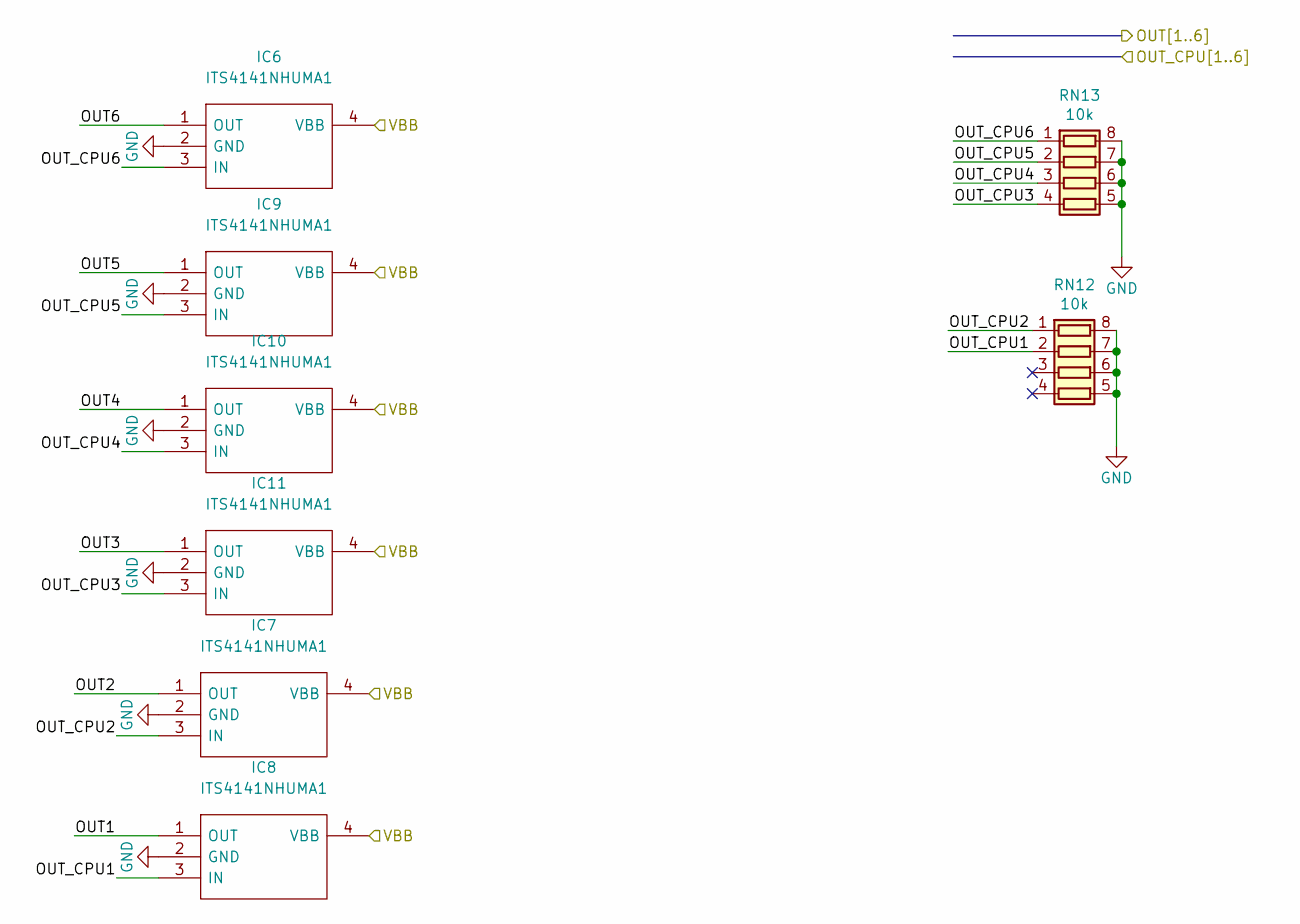
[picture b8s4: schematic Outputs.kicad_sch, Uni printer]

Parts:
IC6, IC7, IC8, IC9, IC10, IC11: ITS4141NHUMA1; SOT230P700X170-4N; Manufacturer_Part_Number ITS4141NHUMA1; Mouser Part Number 726-ITS4141NHUMA1
RN12, RN13: 10k; R_Array_Convex_4x0603

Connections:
/Connectors/OUT_HSW1: IC8.1 (OUT); also elsewhere on the board
/Connectors/OUT_HSW2: IC7.1 (OUT); also elsewhere on the board
/Connectors/OUT_HSW3: IC11.1 (OUT); also elsewhere on the board
/Connectors/OUT_HSW4: IC10.1 (OUT); also elsewhere on the board
/Connectors/OUT_HSW5: IC9.1 (OUT); also elsewhere on the board
/Connectors/OUT_HSW6: IC6.1 (OUT); also elsewhere on the board
/Connectors/SUPPY+: IC6.4 (VBB), IC7.4 (VBB), IC8.4 (VBB), IC9.4 (VBB), IC10.4 (VBB), IC11.4 (VBB); also elsewhere on the board
/OUT_CPU1: IC8.3 (IN), RN12.2 (R2.1); also elsewhere on the board
/OUT_CPU2: IC7.3 (IN), RN12.1 (R1.1); also elsewhere on the board
/OUT_CPU3: IC11.3 (IN), RN13.4 (R4.1); also elsewhere on the board
/OUT_CPU4: IC10.3 (IN), RN13.3 (R3.1); also elsewhere on the board
/OUT_CPU5: IC9.3 (IN), RN13.2 (R2.1); also elsewhere on the board
/OUT_CPU6: IC6.3 (IN), RN13.1 (R1.1); also elsewhere on the board
